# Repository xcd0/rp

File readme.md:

# RP2040を直接実装した自作キーボードを作成する

いきなりは難しいので最初にRaspberry Pi Pico相当のものを作成して、動作確認し、  
そのうえで作成する。  
完成は春節前を目標とする。  

* [調査1](./1.md)
* [調査2](./2.md)
* [試作1](./rp2040_slim_v1/rp2040_slim_v1.md)
* [試作2](./rp2040_slim_v2/rp2040_slim_v2.md)

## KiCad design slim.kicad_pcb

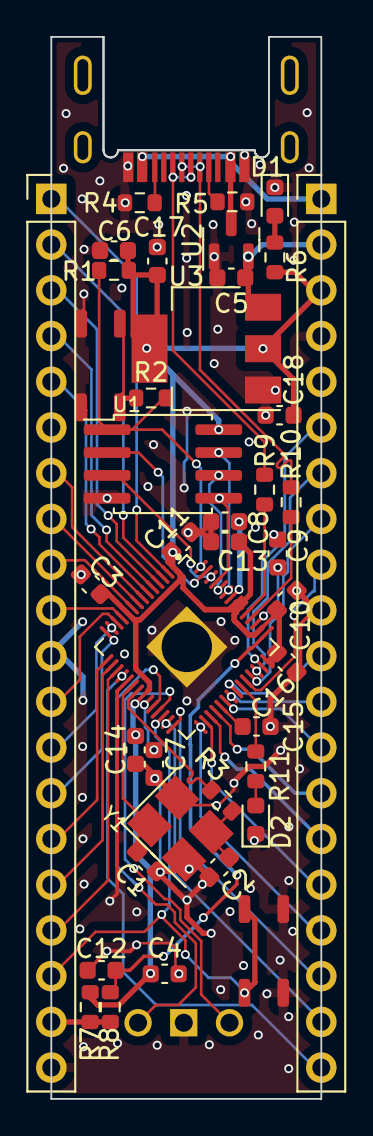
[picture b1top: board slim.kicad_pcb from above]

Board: 2 copper layers, 15.0 x 59.0 mm, 42 parts (0 on the bottom side), 58 nets.

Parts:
BOOT: SW_Push; SKRPABE010
C1, C2: 27p; C_0603_1608Metric
C3, C5, C6: 10u; C_0603_1608Metric
C4, C7, C8, C11, C13, C14, C15, C16, C17, C18: 100n; C_0603_1608Metric
C9, C10, C12: 1u; C_0603_1608Metric
CH1: SWD; SWD_PIN
D1: RED; LED_0603_1608Metric
D2: BLUE; LED_0603_1608Metric
J1: 217179-0001; USB-C-12-Pin-MidMount-ali-v2
J2, J8: Conn_01x20_Pin; PinHeader_1x20_P2.54mm_Vertical
R1, R4, R5, R6: 5.1k; R_0603_1608Metric
R2, R3: 1k; R_0603_1608Metric
R7: 200; R_0603_1608Metric
R8: 1R; R_0603_1608Metric
R9, R10: 27; R_0603_1608Metric
R11: 10k; R_0603_1608Metric
RUN: SW_Push; SKRPABE010
U1: W25Q32JVS; W25Q16-128JV-SOIC
U2: CH213K; SOT-23
U3: AMS1117-3.3; Regulator-AMS1117-SOT-223
U4: RP2040; RP2040_hand
Y1: 12M; Crystal_SMD_3225-4Pin_3.2x2.5mm_HandSoldering

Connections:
+1V1: C7.1, C8.1, C9.1, U4.23 (DVDD), U4.45 (VREG_VOUT), U4.50 (DVDD)
+3V3: C3.1, C4.1, C6.1, C10.1, C11.1, C13.1, C14.1, C15.1, C16.1, C17.1, C18.1, J2.3, R1.2, R6.2, R7.2, U1.8 (VCC), U3.2 (VO), U4.1 (IOVDD), U4.10 (IOVDD), U4.22 (IOVDD), U4.33 (IOVDD), U4.42 (IOVDD), U4.44 (VREG_IN), U4.48 (USB_VDD), U4.49 (IOVDD)
+5V: C5.1, J2.2, U2.2 (VO-), U3.3 (VI)
/ADC_VREF: J8.19, R7.1, R8.2
/BOOTSEL: BOOT.2, R2.1
/GPIO0: J8.1, U4.2 (GPIO0)
/GPIO1: J8.2, U4.3 (GPIO1)
/GPIO2: J8.3, U4.4 (GPIO2)
/GPIO3: J8.4, U4.5 (GPIO3)
/GPIO4: J8.5, U4.6 (GPIO4)
/GPIO5: J8.7, U4.7 (GPIO5)
/GPIO6: J8.8, U4.8 (GPIO6)
/GPIO7: J8.9, U4.9 (GPIO7)
/GPIO8: J8.10, U4.11 (GPIO8)
/GPIO9: J8.12, U4.12 (GPIO9)
/GPIO10: J8.13, U4.13 (GPIO10)
/GPIO11: J8.14, U4.14 (GPIO11)
/GPIO12: J8.15, U4.15 (GPIO12)
/GPIO13: J8.16, U4.16 (GPIO13)
/GPIO14: J8.17, U4.17 (GPIO14)
/GPIO15: J2.20, U4.18 (GPIO15)
/GPIO16: J2.19, U4.27 (GPIO16)
/GPIO17: J2.18, U4.28 (GPIO17)
/GPIO18: J2.17, U4.29 (GPIO18)
/GPIO19: J2.16, U4.30 (GPIO19)
/GPIO20: J2.15, U4.31 (GPIO20)
/GPIO21: J2.14, U4.32 (GPIO21)
/GPIO22: J2.13, U4.34 (GPIO22)
/GPIO23: J2.12, U4.35 (GPIO23)
/GPIO24: J2.11, U4.36 (GPIO24)
/GPIO25: R11.1, U4.37 (GPIO25)
/GPIO26_ADC0: J2.9, U4.38 (GPIO26_ADC0)
/GPIO27_ADC1: J2.8, U4.39 (GPIO27_ADC1)
/GPIO28_ADC2: J2.7, U4.40 (GPIO28_ADC2)
/GPIO29_ADC3: J2.6, U4.41 (GPIO29_ADC3)
/LED: D2.2 (A), R11.2
/QSPI_SCLK: U1.6 (CLK), U4.52 (QSPI_SCLK)
/QSPI_SD0: U1.5 (DI(IO0)), U4.53 (QSPI_SD0)
/QSPI_SD1: U1.2 (DO(IO1)), U4.55 (QSPI_SD1)
/QSPI_SD2: U1.3 (IO2), U4.54 (QSPI_SD2)
/QSPI_SD3: U1.7 (IO3), U4.51 (QSPI_SD3)
/QSPI_SS: R1.1, R2.2, U1.1 (~CS), U4.56 (QSPI_SS)
/RUN: J8.18, RUN.2, U4.26 (RUN)
/SWCLK: CH1.1 (SWCLK), U4.24 (SWCLK)
/SWDIO: CH1.3 (SWDIO), U4.25 (SWD)
/USB_D+: J1.6 (D+_A6), J1.8 (D+_B6), R9.1
/USB_D-: J1.5 (D-_B7), J1.7 (D-_A7), R10.1
/XIN: C1.1, U4.20 (XIN), Y1.1
/XOUT: R3.1, U4.21 (XOUT)
GND: BOOT.1, C1.2, C2.2, C3.2, C4.2, C5.2, C6.2, C7.2, C8.2, C9.2, C10.2, C11.2, C12.2, C13.2, C14.2, C15.2, C16.2, C17.2, C18.2, CH1.2 (GND), D1.1 (K), D2.1 (K), J1.1 (GND_A1/B12), J1.12 (GND_A12/B1), J2.4, J2.5, J2.10, J8.6, J8.11, J8.20, R4.2, R5.2, RUN.1, U1.4 (GND), U2.1 (GND), U3.1 (GND), U4.19 (TESTEN), U4.57 (GND), Y1.2, Y1.4
unnamed: C2.1, R3.2, Y1.3
unnamed: D1.2 (A), R6.1
unnamed: J1.4 (CC1_A5), R5.1
unnamed: J1.10 (CC2_B5), R4.1
unnamed: C12.1, R8.1, U4.43 (ADC_AVDD)
unnamed: R10.2, U4.46 (USB_DM)
unnamed: R9.2, U4.47 (USB_DP)
VBUS: J1.2 (VBUS_A4/B9), J1.11 (VBUS_B4/A9), J2.1, U2.3 (VI+)

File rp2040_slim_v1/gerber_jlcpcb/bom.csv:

Designator,Footprint,Quantity,Value,LCSC Part #
"BOOT, RUN",SKRPABE010,2,SW_Push,
"C1, C2",0603,2,27p,
"C10, C12, C9",0603,3,1u,
"C11, C13, C14, C15, C16, C17, C18, C4, C7, C8",0603,10,100n,
"C3, C5, C6",0603,3,10u,
CH1,SWD_PIN,1,SWD,
D1,0603,1,RED,
D2,0603,1,BLUE,
J1,USB-C-12-Pin-MidMount-ali-v2,1,217179-0001,
"J2, J8",PinHeader_1x20_P2.54mm_Vertical,2,Conn_01x20_Pin,
"R1, R4, R5, R6",0603,4,5.1k,
"R10, R9",0603,2,27,
R11,0603,1,10k,
"R2, R3",0603,2,1k,
R7,0603,1,200,
R8,0603,1,1R,
U1,W25Q16-128JV-SOIC,1,W25Q32JVS,
U2,SOT-23,1,CH213K,
U3,Regulator-AMS1117-SOT-223,1,AMS1117-3.3,
U4,RP2040_hand,1,RP2040,
Y1,Crystal_SMD_3225-4Pin_3.2x2.5mm_HandSoldering,1,12M,

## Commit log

2024-01-20 docs: update 2024.01.21.04:37.53
2024-01-20 docs: update 2024.01.21.04:39.18
2024-01-20 docs: update 2024.01.21.04:40.09
2024-01-20 docs: update 2024.01.21.04:41.42
2024-01-20 docs: update 2024.01.21.04:42.04
2024-01-20 docs: update 2024.01.21.04:42.21
2024-01-20 docs: update 2024.01.21.04:44.13
2024-01-20 docs: update 2024.01.21.04:44.38
2024-01-20 docs: update 2024.01.21.04:44.59
2024-01-20 docs: update 2024.01.21.05:13.12
